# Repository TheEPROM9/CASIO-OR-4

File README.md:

# CASIO-OR-4
Schematices, design files &amp; everything I have on revercse engineering efforts on the CASIO OR-4 4-BIT 4KB RAM module. If any of you guys can contrubute to this then go ahead, for example using a more modern RAM chip.

I intend to have these as Open Source projects so the comunity can edit & improve the design files. I am hopeing we can find a way to use modern RAM chips so we can truyely make repoductions of these RAM cards as original ones are hard to find & exspnsive.

Link to project: [CASIO OR-4 RAM Pack](https://www.theeprom9.co.uk/vintage-computers/reverse-engineering-computers/casio-or-4-ram-pack)

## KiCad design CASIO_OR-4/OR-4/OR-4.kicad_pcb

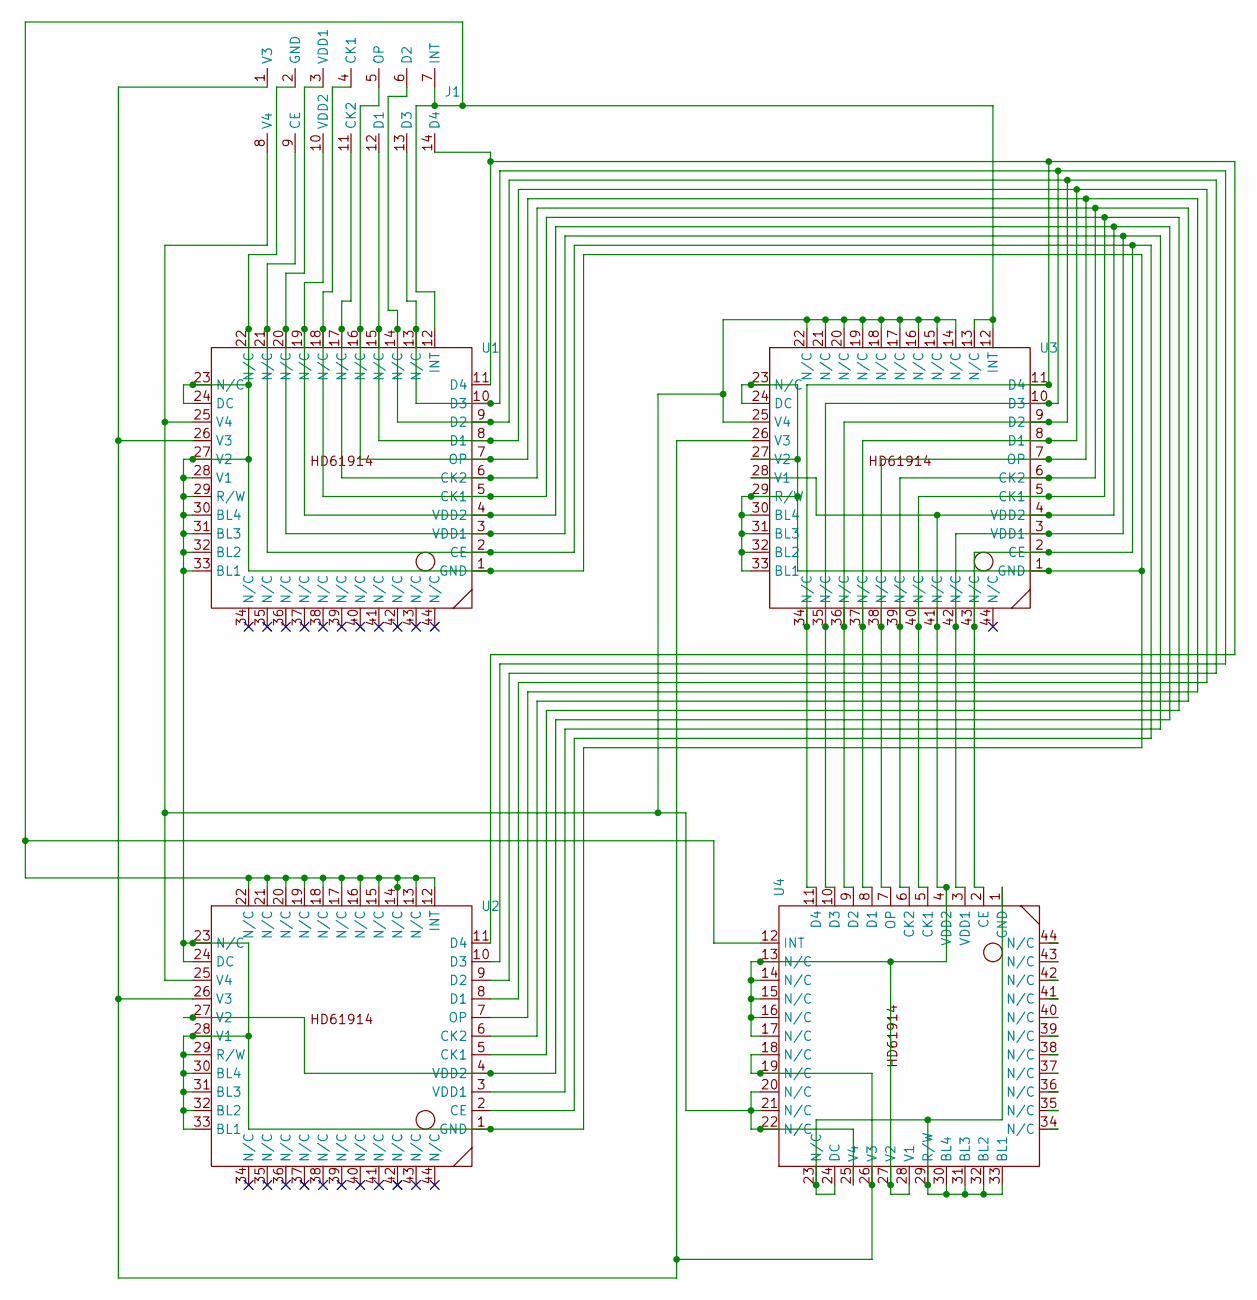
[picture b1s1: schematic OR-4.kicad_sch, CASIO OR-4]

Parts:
J1: CASIO_OR-4_RAM_Pin_Header
U1, U2, U3, U4: HD61914

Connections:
unnamed: J1.9 (CE), U1.2 (CE), U1.21 (N/C), U2.2 (CE), U3.2 (CE), U3.43 (N/C), U4.2 (CE)
unnamed: J1.4 (CK1), U1.5 (CK1), U1.18 (N/C), U2.5 (CK1), U3.5 (CK1), U3.40 (N/C), U4.5 (CK1)
unnamed: J1.11 (CK2), U1.6 (CK2), U1.17 (N/C), U2.6 (CK2), U3.6 (CK2), U3.39 (N/C), U4.6 (CK2)
unnamed: J1.12 (D1), U1.8 (D1), U1.15 (N/C), U2.8 (D1), U3.8 (D1), U3.37 (N/C), U4.8 (D1)
unnamed: J1.6 (D2), U1.9 (D2), U1.14 (N/C), U2.9 (D2), U3.9 (D2), U3.36 (N/C), U4.9 (D2)
unnamed: J1.13 (D3), U1.10 (D3), U1.13 (N/C), U2.10 (D3), U3.10 (D3), U3.35 (N/C), U4.10 (D3)
unnamed: J1.14 (D4), U1.11 (D4), U2.11 (D4), U3.11 (D4), U3.34 (N/C), U4.11 (D4)
unnamed: J1.2 (GND), U1.1 (GND), U1.22 (N/C), U1.23 (N/C), U1.24 (DC), U1.27 (V2), U1.28 (V1), U1.29 (R/W), U1.30 (BL4), U1.31 (BL3), U1.32 (BL2), U1.33 (BL1), U2.1 (GND), U2.23 (N/C), U2.24 (DC), U2.28 (V1), U2.29 (R/W), U2.30 (BL4), U2.31 (BL3), U2.32 (BL2), U2.33 (BL1), U3.1 (GND), U3.23 (N/C), U3.24 (DC), U3.27 (V2), U3.29 (R/W), U3.30 (BL4), U3.31 (BL3), U3.32 (BL2), U3.33 (BL1)
unnamed: J1.7 (INT), U1.12 (INT), U2.12 (INT), U2.13 (N/C), U2.14 (N/C), U2.15 (N/C), U2.16 (N/C), U2.17 (N/C), U2.18 (N/C), U2.19 (N/C), U2.20 (N/C), U2.21 (N/C), U2.22 (N/C), U3.12 (INT), U3.13 (N/C), U4.12 (INT)
unnamed: J1.5 (OP), U1.7 (OP), U1.16 (N/C), U2.7 (OP), U3.7 (OP), U3.38 (N/C), U4.7 (OP)
unnamed: J1.1 (V3), U1.26 (V3), U2.26 (V3), U3.26 (V3), U4.18 (N/C), U4.19 (N/C), U4.26 (V3)
unnamed: J1.8 (V4), U1.25 (V4), U2.25 (V4), U3.14 (N/C), U3.15 (N/C), U3.16 (N/C), U3.17 (N/C), U3.18 (N/C), U3.19 (N/C), U3.20 (N/C), U3.21 (N/C), U3.22 (N/C), U3.25 (V4), U4.20 (N/C), U4.21 (N/C), U4.22 (N/C), U4.25 (V4)
unnamed: J1.3 (VDD1), U1.3 (VDD1), U1.20 (N/C), U2.3 (VDD1), U3.3 (VDD1), U3.42 (N/C), U4.3 (VDD1)
unnamed: J1.10 (VDD2), U1.4 (VDD2), U1.19 (N/C), U2.4 (VDD2), U2.27 (V2), U3.4 (VDD2), U3.28 (V1), U3.41 (N/C), U4.4 (VDD2), U4.13 (N/C), U4.14 (N/C), U4.15 (N/C), U4.16 (N/C), U4.17 (N/C), U4.27 (V2), U4.28 (V1)
unnamed: U4.1 (GND), U4.23 (N/C), U4.24 (DC), U4.29 (R/W), U4.30 (BL4), U4.31 (BL3), U4.32 (BL2), U4.33 (BL1)

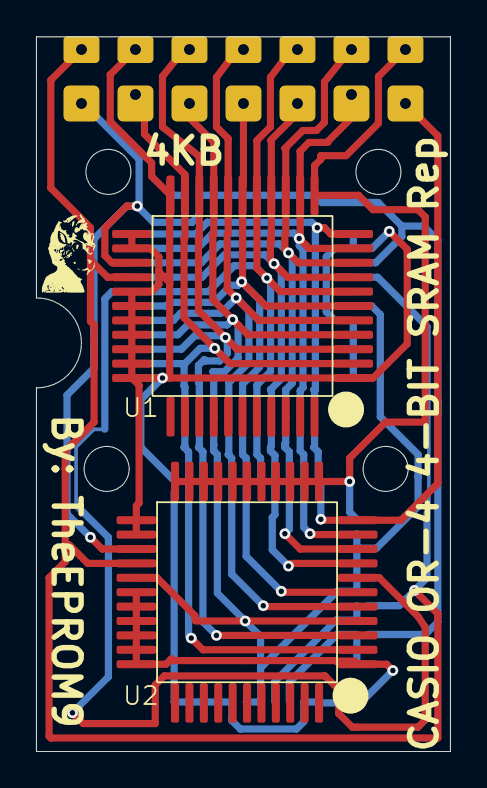
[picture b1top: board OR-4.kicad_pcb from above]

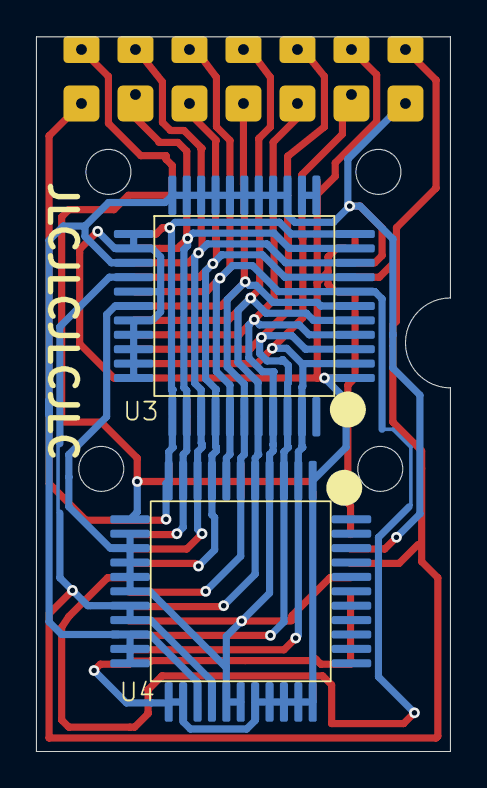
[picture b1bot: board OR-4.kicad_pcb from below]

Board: 2 copper layers, 23.0 x 39.7 mm, 5 parts (2 on the bottom side), 15 nets.

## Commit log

2025-10-15 First Bulk Upload
    Same as the last one. Will be updated based on mistakes found & improvements made to the design.
2025-10-16 Update README.md
    Added link to project page.
2025-10-16 Updated Hole Spaceing
    Bottom holes were incorrect.
2025-10-16 Removed Dimetions Clutter
